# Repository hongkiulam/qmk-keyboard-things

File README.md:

#### `./docker_qmk_bash.sh`
Starts an interactive shell where the qmk cli is available

#### `.docker_qmk_compile.sh {keyboard} {keymap}`
Attempts to compile the keyboard

#### `./docker_qmk_flash.sh {keyboard} {keymap}`
Attempts to flash the keyboard

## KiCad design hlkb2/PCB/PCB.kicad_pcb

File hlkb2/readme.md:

### hlkb2

My second custom keyboard build which is a 40% membrane keyboard.

The motivation is that I'm a huge fan of the 40% form factor as well as the customisation that QMK provides, but didn't find the cost of building with mechanical switches worth it. Membrane keyboards have always been far cheaper than mechanical so I was interested to see if it would be possible to make a cheaper 40% QMK enabled keyboard with membrane parts.

Final Cost: TBC

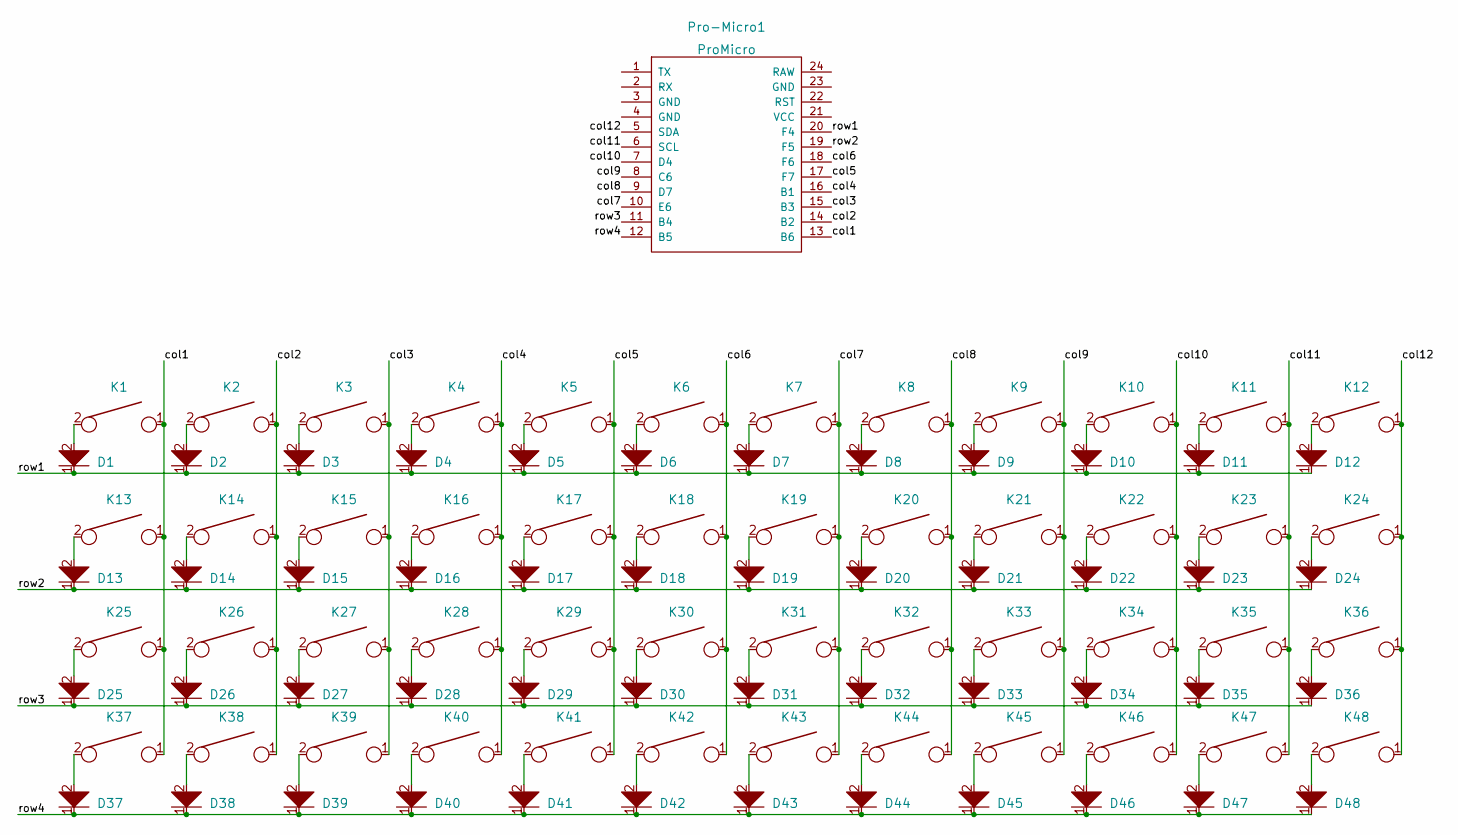
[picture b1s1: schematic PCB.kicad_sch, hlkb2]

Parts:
D1, D2, D3, D4, D5, D6, D7, D8, D9, D10, D11, D12, D13, D14, D15, D16, D17, D18, D19, D20, D21, D22, D23, D24, D25, D26, D27, D28, D29, D30, D31, D32, D33, D34, D35, D36, D37, D38, D39, D40, D41, D42, D43, D44, D45, D46, D47, D48: D; D_SOD123_axial
K1, K2, K3, K4, K5, K6, K7, K8, K9, K10, K11, K12, K13, K14, K15, K16, K17, K18, K19, K20, K21, K22, K23, K24, K25, K26, K27, K28, K29, K30, K31, K32, K33, K34, K35, K36, K37, K38, K39, K40, K41, K42, K43, K44, K45, K46, K47, K48: KEYSW
Pro-Micro1: ProMicro

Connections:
/col1: K1.1, K13.1, K25.1, K37.1, Pro-Micro1.13 (B6)
/col2: K2.1, K14.1, K26.1, K38.1, Pro-Micro1.14 (B2)
/col3: K3.1, K15.1, K27.1, K39.1, Pro-Micro1.15 (B3)
/col4: K4.1, K16.1, K28.1, K40.1, Pro-Micro1.16 (B1)
/col5: K5.1, K17.1, K29.1, K41.1, Pro-Micro1.17 (F7)
/col6: K6.1, K18.1, K30.1, K42.1, Pro-Micro1.18 (F6)
/col7: K7.1, K19.1, K31.1, K43.1, Pro-Micro1.10 (E6)
/col8: K8.1, K20.1, K32.1, K44.1, Pro-Micro1.9 (D7)
/col9: K9.1, K21.1, K33.1, K45.1, Pro-Micro1.8 (C6)
/col10: K10.1, K22.1, K34.1, K46.1, Pro-Micro1.7 (D4)
/col11: K11.1, K23.1, K35.1, K47.1, Pro-Micro1.6 (SCL)
/col12: K12.1, K24.1, K36.1, K48.1, Pro-Micro1.5 (SDA)
/row1: D1.1, D2.1, D3.1, D4.1, D5.1, D6.1, D7.1, D8.1, D9.1, D10.1, D11.1, D12.1, Pro-Micro1.20 (F4)
/row2: D13.1, D14.1, D15.1, D16.1, D17.1, D18.1, D19.1, D20.1, D21.1, D22.1, D23.1, D24.1, Pro-Micro1.19 (F5)
/row3: D25.1, D26.1, D27.1, D28.1, D29.1, D30.1, D31.1, D32.1, D33.1, D34.1, D35.1, D36.1, Pro-Micro1.11 (B4)
/row4: D37.1, D38.1, D39.1, D40.1, D41.1, D42.1, D43.1, D44.1, D45.1, D46.1, D47.1, D48.1, Pro-Micro1.12 (B5)
unnamed: D1.2, K1.2
unnamed: D2.2, K2.2
unnamed: D3.2, K3.2
unnamed: D4.2, K4.2
unnamed: D5.2, K5.2
unnamed: D6.2, K6.2
unnamed: D7.2, K7.2
unnamed: D8.2, K8.2
unnamed: D9.2, K9.2
unnamed: D10.2, K10.2
unnamed: D11.2, K11.2
unnamed: D12.2, K12.2
unnamed: D13.2, K13.2
unnamed: D14.2, K14.2
unnamed: D15.2, K15.2
unnamed: D16.2, K16.2
unnamed: D17.2, K17.2
unnamed: D18.2, K18.2
unnamed: D19.2, K19.2
unnamed: D20.2, K20.2
unnamed: D21.2, K21.2
unnamed: D22.2, K22.2
unnamed: D23.2, K23.2
unnamed: D24.2, K24.2
unnamed: D25.2, K25.2
unnamed: D26.2, K26.2
unnamed: D27.2, K27.2
unnamed: D28.2, K28.2
unnamed: D29.2, K29.2
unnamed: D30.2, K30.2
unnamed: D31.2, K31.2
unnamed: D32.2, K32.2
unnamed: D33.2, K33.2
unnamed: D34.2, K34.2
unnamed: D35.2, K35.2
unnamed: D36.2, K36.2
unnamed: D37.2, K37.2
unnamed: D38.2, K38.2
unnamed: D39.2, K39.2
unnamed: D40.2, K40.2
unnamed: D41.2, K41.2
unnamed: D42.2, K42.2
unnamed: D43.2, K43.2
unnamed: D44.2, K44.2
unnamed: D45.2, K45.2
unnamed: D46.2, K46.2
unnamed: D47.2, K47.2
unnamed: D48.2, K48.2

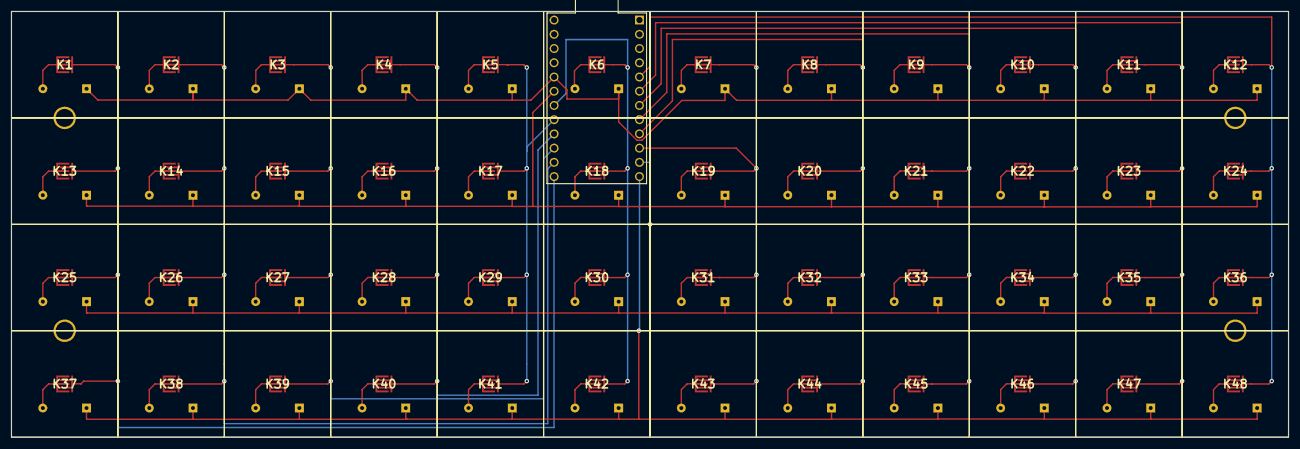
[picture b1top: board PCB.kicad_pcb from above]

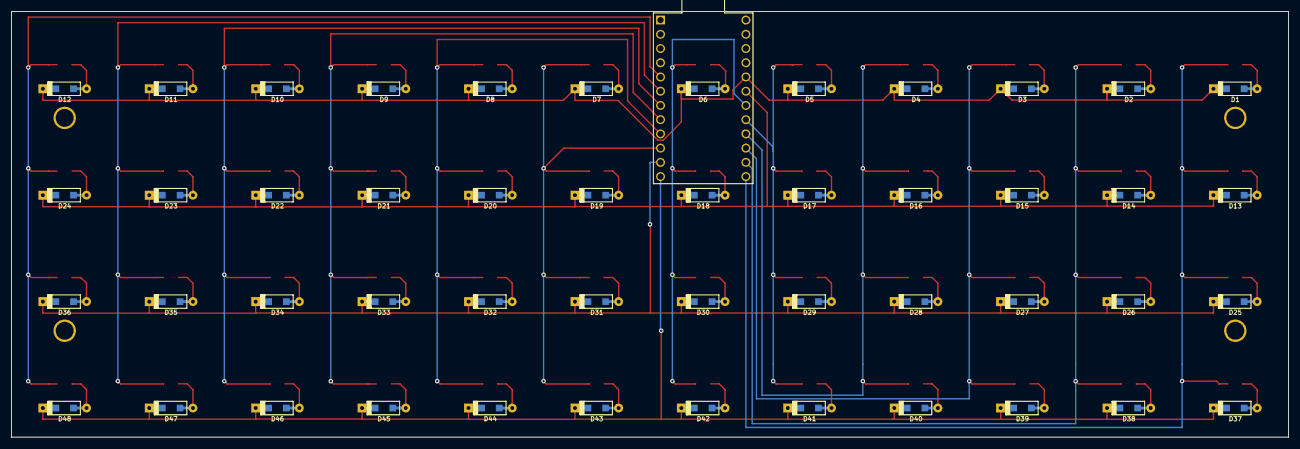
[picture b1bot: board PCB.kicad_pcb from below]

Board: 2 copper layers, 228.0 x 76.0 mm, 101 parts (49 on the bottom side), 64 nets.

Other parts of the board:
HOLE_M3, HOLE_M3#2, HOLE_M3#3, HOLE_M3#4: VAL**; HOLE_M3

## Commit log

2020-09-22 Commit files
2020-09-22 Add useState macro and . on numpad
2020-09-26 Move common keys to more accessible layer (I think)
2020-12-03 Add tab to layer 3, add F keys to layer 4
2021-06-27 Move hk_40_kb into sub folder
2021-06-27 Add basic firmware files generated by kbfirmware.com
2021-06-27 Add qmkbuilder
2021-06-27 Add qmk_firmware fork as submobule
2021-11-03 Create proper keyboard source files, compile and flash with docker
2021-11-05 More readable info.json
2021-11-21 Add hjkl tap dance for arrow keys
2022-02-21 Replace tap dance directional keys with hjkl on third layer
2022-03-07 Swap ESC and CAPS key
2022-03-12 Commit new keyboard generated by qmk new-keyboard
2022-03-19 Update hlkb2 bootloader to caterina, add labels to layout
2022-03-19 Add keyboard-layout-editor json that wasn't commited before?
2022-03-19 hlkb2 pcb v1
2022-03-21 Add some readme's, remove qmkbuilder docker-compose file
2022-03-23 Swap TAB and CAPS between first and second layer
2022-04-01 Define keyboard pin mappings, add a dimension to KiCAD PCB
2022-04-02 CAD Files - PCB, Pro Micro, Case, Domes
2022-04-17 Add new keymap for hlkb1
2022-04-17 Add 3mm contact pad, update PCB
2022-04-18 Arrow function macro doesn't move back to arg bracket
2022-04-20 hlkb1:default update numpad, add brightness volume controls
2023-04-08 Fix all issues related to using newest QMK version
2023-05-20 Add default keychron via map
2023-05-20 Fix default
